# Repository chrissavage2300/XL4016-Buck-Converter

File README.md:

# XL4016-Buck-Converter
XL4016 Buck Converter done in eagle cad. This is my own version of the popular XL4016 board. The XL4016's were bought from LCSC. 

NOTE THIS IS UNTESTED

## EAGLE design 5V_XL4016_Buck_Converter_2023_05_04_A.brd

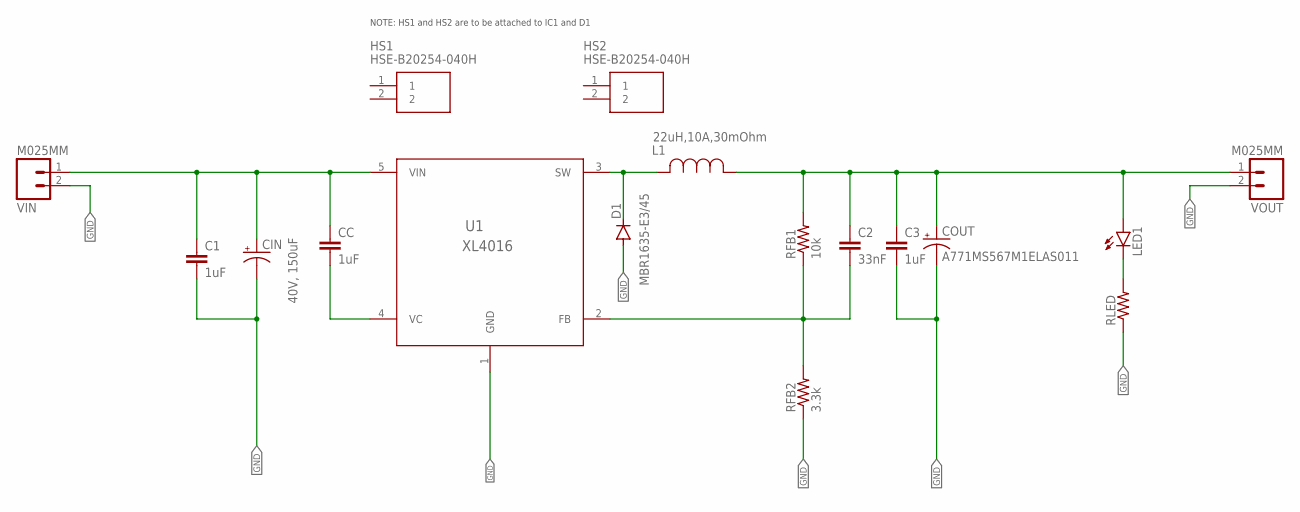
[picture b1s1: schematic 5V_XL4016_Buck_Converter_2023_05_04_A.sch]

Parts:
C1, C3: 1uF; 0805
C2: 33nF; 0805
CC: 1uF; 0805
CIN: 40V, 150uF; CAP_A768_KEM-M
COUT: A771MS567M1ELAS011; 153CLV-1012
D1: MBR1635-E3/45; DO220S
HS1, HS2: HSE-B20254-040H; HSEB20254040H
L1: 22uH,10A,30mOhm; IND_SRP1265C-LEADFRAME_BRN-M
LED1: LED1206; LED-1206
RFB1: 10k; 0805
RFB2: 3.3k; 0805
RLED: RESISTOR0805-RES; 0805
U1: XL4016; TO220-5L
VIN: M025MM; SCREWTERMINAL-5MM-2
VOUT: M025MM; SCREWTERMINAL-5MM-2

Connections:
FB: C2.2, RFB1.1, RFB2.2, U1.2 (FB)
GND: C1.2, C3.2, CIN.2 (-), COUT.-, D1.A, RFB2.1, RLED.1, U1.1 (GND), VIN.2, VOUT.2
unnamed: LED1.C, RLED.2
SW: D1.C, L1.2, U1.3 (SW)
VC: CC.2, U1.4 (VC)
VIN: C1.1, CC.1, CIN.1 (+), U1.5 (VIN), VIN.1
VOUT: C2.1, C3.1, COUT.+, L1.1, LED1.A, RFB1.2, VOUT.1

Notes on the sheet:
NOTE: HS1 and HS2 are to be attached to IC1 and D1

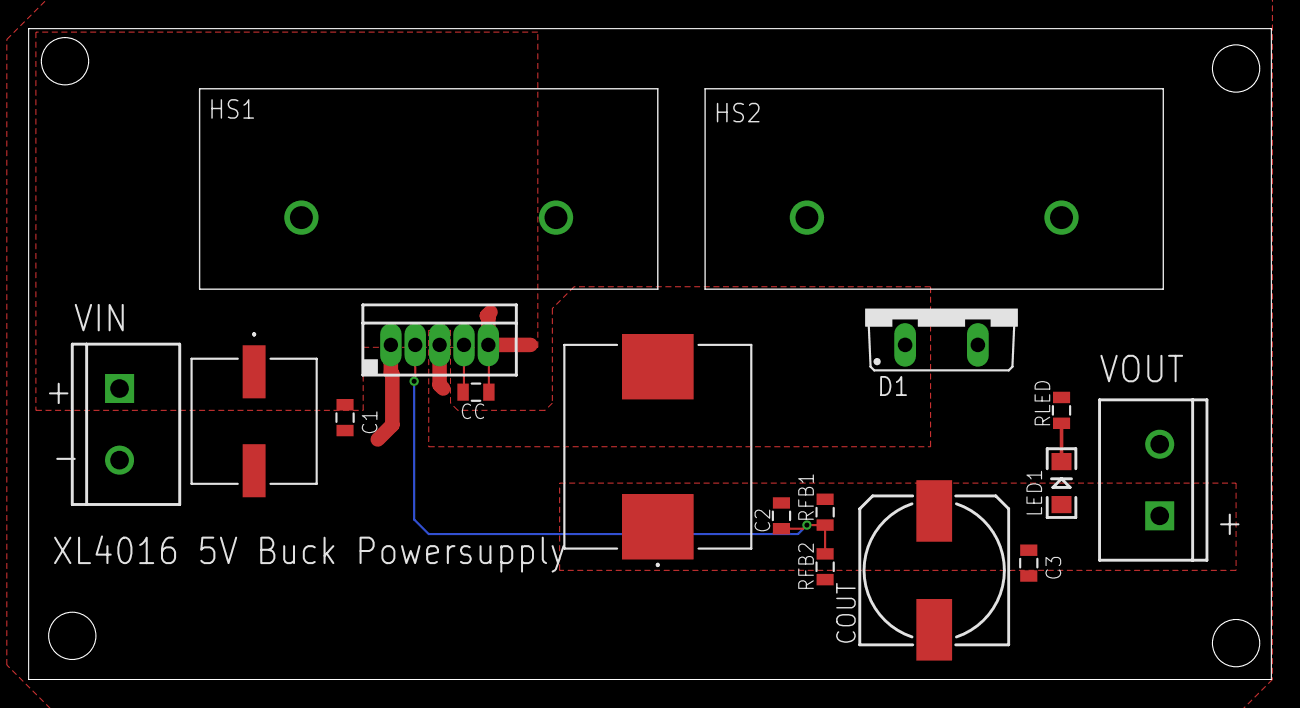
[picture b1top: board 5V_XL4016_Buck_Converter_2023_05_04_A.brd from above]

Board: 2 copper layers, 86.8 x 45.5 mm, 17 parts (0 on the bottom side), 7 nets.

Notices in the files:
parts and their libraries:
SparkFun-Capacitors: Licensing: Creative Commons ShareAlike 4.0 International - https://creativecommons.org/licenses/by-sa/4.0
COPYRIGHT: Copyright (C) 2023 Ultra Librarian. All rights reserved.
